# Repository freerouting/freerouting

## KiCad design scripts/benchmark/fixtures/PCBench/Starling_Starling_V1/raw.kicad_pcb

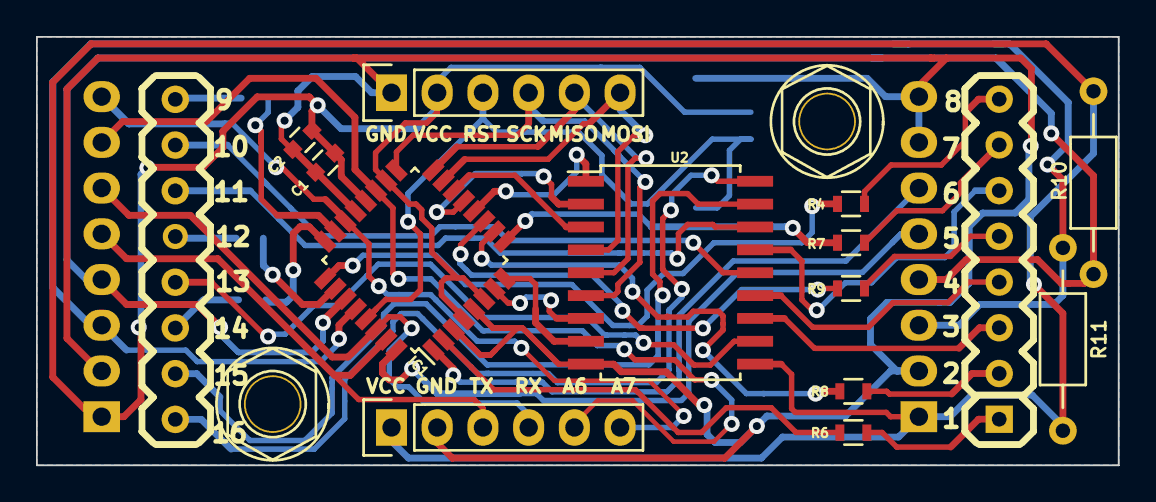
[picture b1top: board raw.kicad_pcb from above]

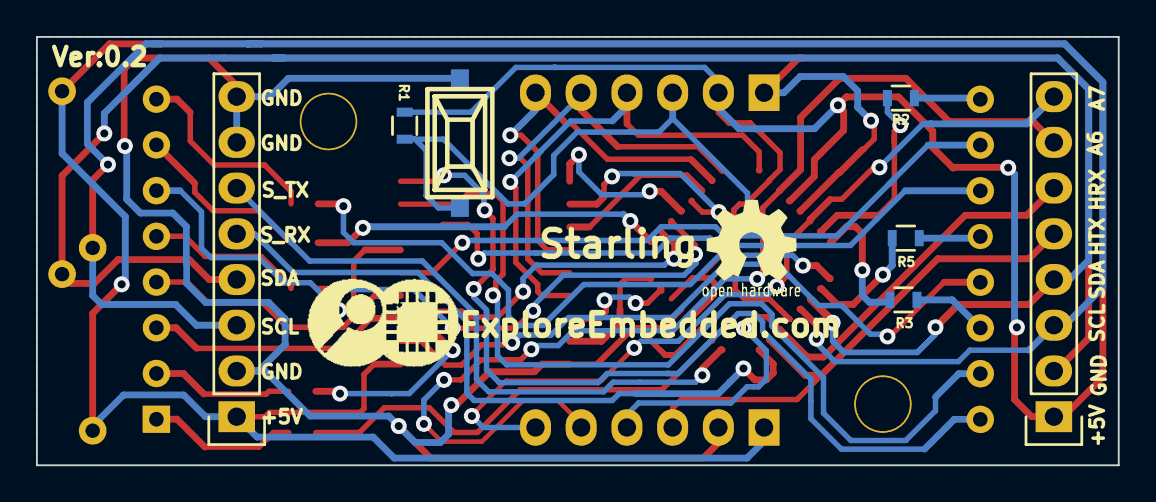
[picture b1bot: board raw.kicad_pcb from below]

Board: 2 copper layers, 60.1 x 23.8 mm, 24 parts (8 on the bottom side), 43 nets.

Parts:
C1, C2: 0.1uF; C_0603
IC1: ATMEGA8-AI; LQFP-32_7x7mm_Pitch0.8mm
LOGO: LOGO (2)
P1, P2: CONN_01X01; M3_mounting
P3, P6: CONN_01X06; Pin_Header_Straight_1x06
P4, P5: CONN_01X08; Pin_Header_Straight_1x08
R1: 10K; R_0603
R2, R3, R4, R5, R6, R7, R8, R9: 22r; R_0603
R10, R11: 10K; Resistor_Horizontal_RM10mm
SW1: SPST; smd_push
U1: 8x8_Row_anode; 8X8_matrix_2.3inch
U2: ULN2803; SOIC-18_7.5x11.6mm_Pitch1.27mm

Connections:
+5C: C1.1, C2.1, IC1.4, IC1.6, IC1.18, IC1.20, P3.2, P4.1, P5.1, P6.1, R1.1, R10.1, R11.1, U2.10
/ADC6: IC1.19, P4.7, P6.5
/ADC7: IC1.22, P4.8, P6.6
/H_RX: IC1.30, P4.6, P6.4
/H_TX: IC1.31, P4.5, P6.3
/MISO: IC1.16, P3.5, U2.5
/MOSI: IC1.15, P3.6, U2.4
/PB6: IC1.7, U2.7
/PB7: IC1.8, U2.8
/RST: IC1.29, P3.3, R1.2, SW1.2
/SCK: IC1.17, P3.4, U2.6
/SCL: IC1.28, P4.3, P5.3, R11.2
/SDA: IC1.27, P4.4, P5.4, R10.2
/S_RX: IC1.32, P5.5
/S_TX: IC1.1, P5.6
GND: C1.2, C2.2, IC1.3, IC1.5, IC1.21, P3.1, P4.2, P5.2, P5.7, P5.8, P6.2, SW1.1, U2.9
unnamed: IC1.2, R6.2
unnamed: IC1.9, R7.2
unnamed: IC1.10, R8.2
unnamed: IC1.11, R9.2
unnamed: IC1.12, U2.1
unnamed: IC1.13, U2.2
unnamed: IC1.14, U2.3
unnamed: IC1.23, R2.2
unnamed: IC1.24, R3.2
unnamed: IC1.25, R4.2
unnamed: IC1.26, R5.2
unnamed: R2.1, U1.9
unnamed: R3.1, U1.14
unnamed: R4.1, U1.8
unnamed: R5.1, U1.12
unnamed: R6.1, U1.1
unnamed: R7.1, U1.7
unnamed: R8.1, U1.2
unnamed: R9.1, U1.5
unnamed: U1.3, U2.12
unnamed: U1.4, U2.13
unnamed: U1.6, U2.15
unnamed: U1.10, U2.14
unnamed: U1.11, U2.16
unnamed: U1.13, U2.11
unnamed: U1.15, U2.17
unnamed: U1.16, U2.18

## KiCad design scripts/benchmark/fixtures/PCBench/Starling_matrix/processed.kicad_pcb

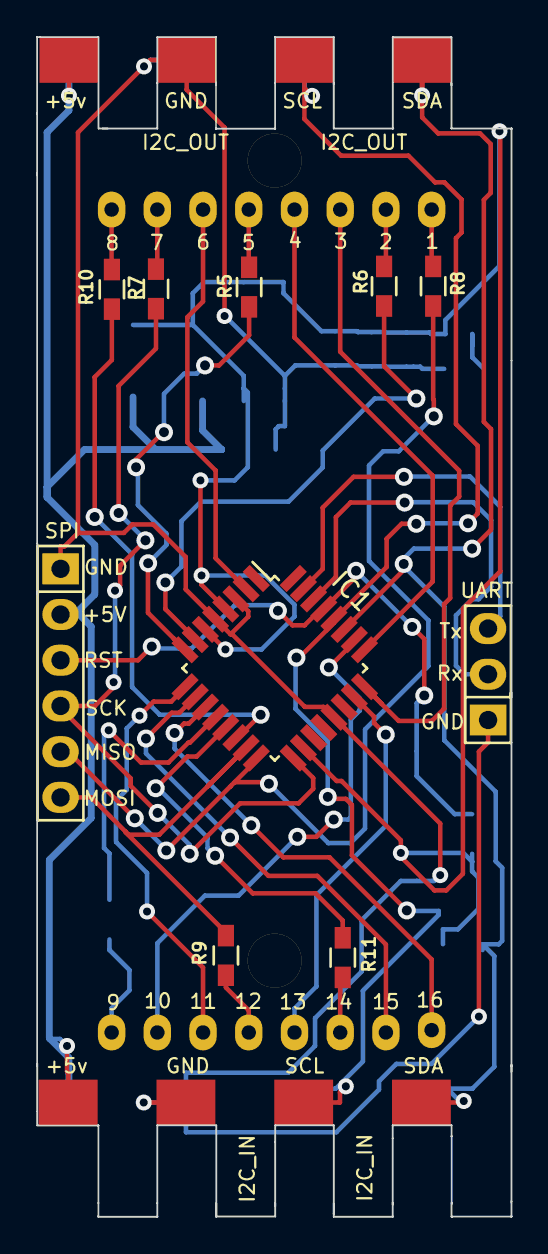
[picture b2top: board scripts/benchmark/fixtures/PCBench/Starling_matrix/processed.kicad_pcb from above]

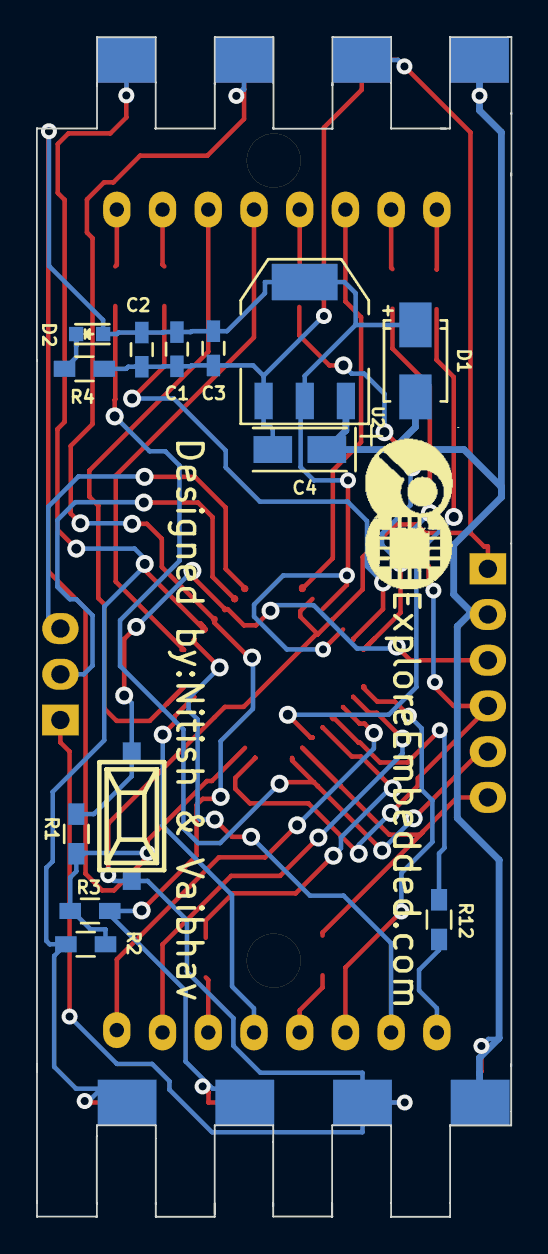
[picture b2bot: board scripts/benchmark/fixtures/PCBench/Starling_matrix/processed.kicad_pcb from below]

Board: 2 copper layers, 26.4 x 65.6 mm, 29 parts (14 on the bottom side), 33 nets.

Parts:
C1, C2, C3: 0.1uf; C_0603_HandSoldering
C4: 10uF; TantalC_SizeA_EIA-3216_Wave
D1: DIODE; SMA_Standard
D2: LED; LED-0603
IC1: ATMEGA8-AI; TQFP-32_7x7mm_Pitch0.8mm
LOGO: LOGO (2)
P1: CONN_01X06; Pin_Header_Straight_1x06
P2, P3: CONN_01X04; matrix_connector
P4: CONN_01X03; Pin_Header_Straight_1x03
P5, P6: CONN_01X01; 1pin
R1, R2, R3: 10K; R_0603_HandSoldering
R4: 470E; R_0603_HandSoldering
R5, R6, R7, R8, R9, R10, R11, R12: 22E; R_0603_HandSoldering
SW1: SPST; smd_push
U1: DispHB2388; 8x8dot matrix
U2: lm1117/3.3; lm117_SOT-223

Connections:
+3V3: C1.1, C2.1, C3.1, D1.1, D2.1, IC1.4, IC1.6, IC1.18, R1.1, R2.1, R3.1, U2.2, U2.4
+5V: C4.1, D1.2, P1.2, P2.1, P3.1, U2.3
/MISO: IC1.16, P1.5, R8.1
/MOSI: IC1.15, P1.6, R9.1
/PB6: IC1.7, R6.1
/PB7: IC1.8, R5.1
/RST: IC1.29, P1.3, R1.2, SW1.2
/Rx: IC1.30, P4.2
/SCK: IC1.17, P1.4, R7.1
/SCL: IC1.28, P2.3, P3.3, R3.2
/SDA: IC1.27, P2.4, P3.4, R2.2
/Tx: IC1.31, P4.3
GND: C1.2, C2.2, C3.2, C4.2, IC1.3, IC1.5, IC1.21, P1.1, P2.2, P3.2, P4.1, R4.2, SW1.1, U2.1
unnamed: D2.2, R4.1
unnamed: IC1.2, U1.6
unnamed: IC1.9, U1.11
unnamed: IC1.10, U1.15
unnamed: IC1.11, U1.16
unnamed: IC1.12, R12.1
unnamed: IC1.13, R11.1
unnamed: IC1.14, R10.1
unnamed: IC1.23, U1.13
unnamed: IC1.24, U1.3
unnamed: IC1.25, U1.4
unnamed: IC1.26, U1.10
unnamed: R5.2, U1.5
unnamed: R6.2, U1.2
unnamed: R7.2, U1.7
unnamed: R8.2, U1.1
unnamed: R9.2, U1.12
unnamed: R10.2, U1.8
unnamed: R11.2, U1.14
unnamed: R12.2, U1.9

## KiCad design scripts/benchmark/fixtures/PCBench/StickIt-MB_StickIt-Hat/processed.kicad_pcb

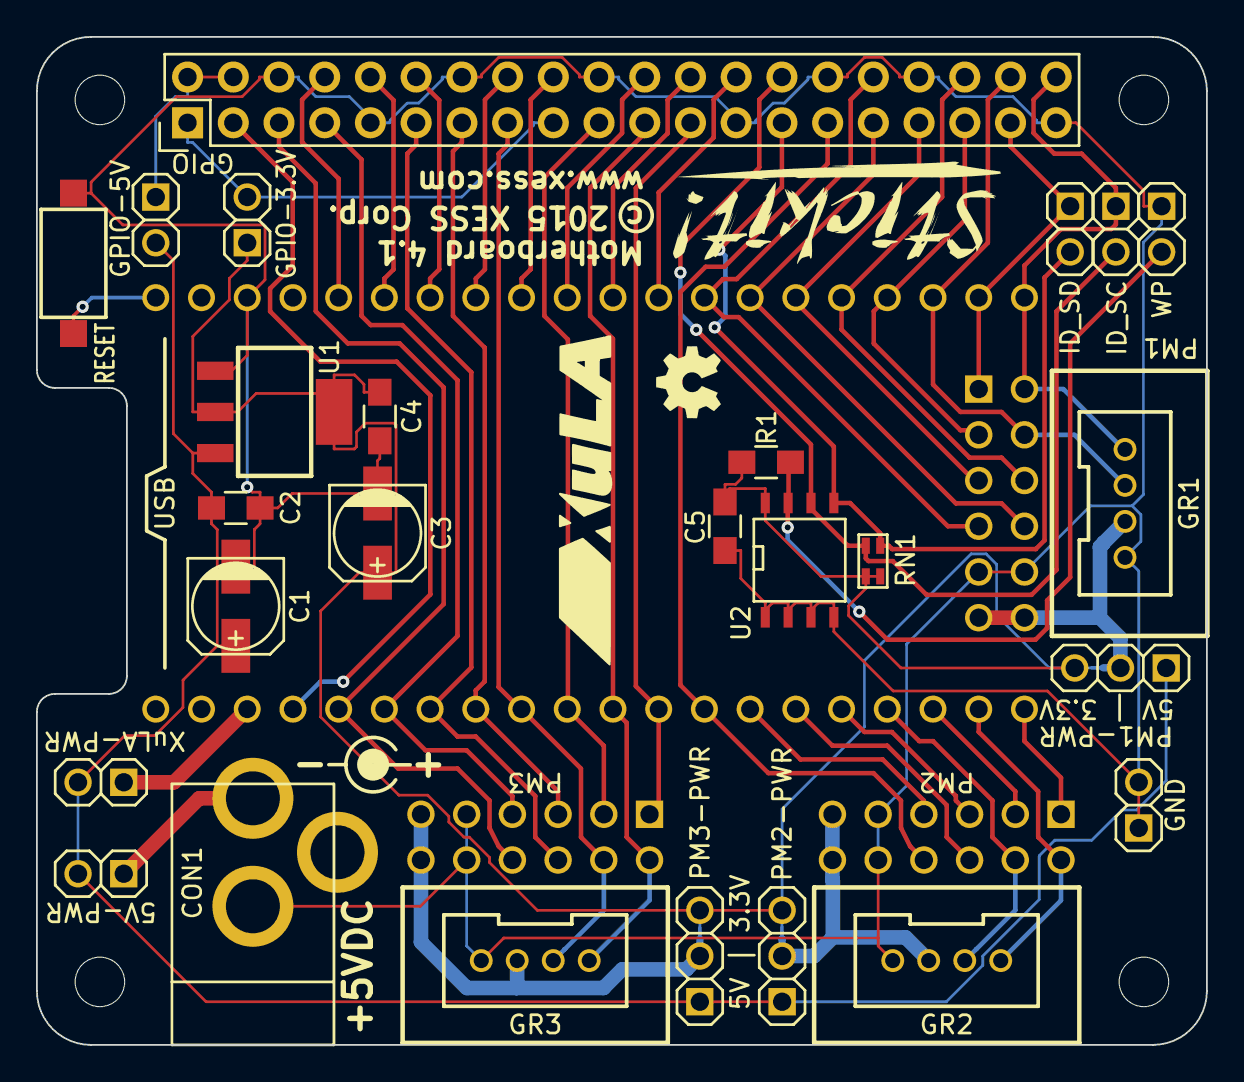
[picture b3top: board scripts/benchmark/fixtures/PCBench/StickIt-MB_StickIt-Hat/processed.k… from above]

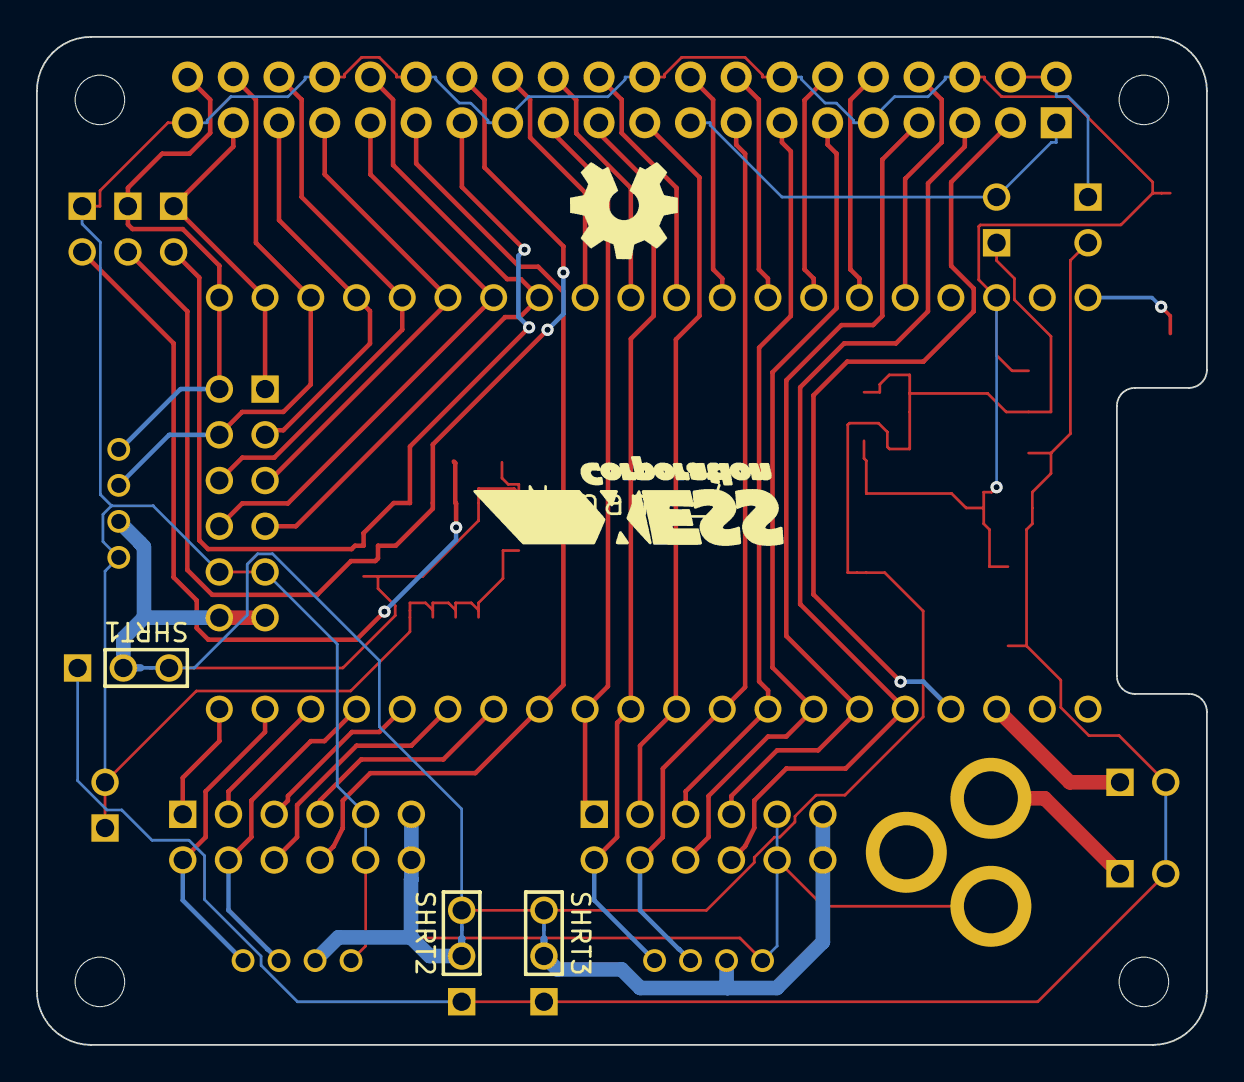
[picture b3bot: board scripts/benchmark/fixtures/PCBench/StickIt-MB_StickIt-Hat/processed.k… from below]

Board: 2 copper layers, 65.0 x 56.0 mm, 41 parts (5 on the bottom side), 47 nets.

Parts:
C1, C3: 22uF; c_elec_5x5.3
C2, C4: 4.7uF; R_0805_HandSoldering
C5: 0.1uF; R_0805_HandSoldering
CON1: BARREL_JACK
GPIO1: RPi_GPIO; Pin_Header_Straight_2x20
GR1, GR2, GR3: Grove; GROVE_MALE
J1: XuLA_IO_HDR; XuLA_IO_Hdr
J3, J4, J5: JSHORTNORMAL; xess-JSHORT
JP1, JP2, JP3: JUMPER3; HDR_1x3
JP4, JP5, JP6, JP7, JP8, JP9, JP10: JUMPER; HDR_1x2
Noname_1: oshw_logo_4mm
Noname_2: stickit_logo_18mm
Noname_3: oshw_logo_6mm
Noname_4: xesscorp2
Noname_5, Noname_6, Noname_7, Noname_8: RPi_Hat_Mounting_Hole
PM1, PM2, PM3: PMOD_SCKT-12
R1: 1K; R_0805_HandSoldering
RN1: 3.9K; CTS_742C043
SW1: SW_PUSH; RS-282G05A3-SM_RT
TP1: JUMPER; HDR_1x2
U1: NCV1117; SOT-223
U2: CAT24C32; SOIC-8-N

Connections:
+3.3V: C3.1, C4.1, C5.1, J3.2, J4.2, J5.2, JP1.3, JP2.3, JP3.3, JP7.1, R1.1, RN1.1, RN1.2, U1.2, U1.4, U2.8
+3.3V-RPi: GPIO1.1, GPIO1.17, JP7.2
+5V: C1.1, C2.1, JP1.1, JP2.1, JP3.1, JP4.2, JP5.2, JP6.2, U1.3
+5V-RPi: GPIO1.2, GPIO1.4, JP4.1
+5V-XuLA: J1.3, JP5.1
CHAN0: GPIO1.37, J1.22, JP10.1, PM1.1
CHAN1: GPIO1.38, GR1.2, J1.23, PM1.8
CHAN2: GPIO1.35, J1.24, PM1.2
CHAN3: GPIO1.36, J1.25, PM1.9
CHAN4: GPIO1.33, J1.26, PM1.3
CHAN5: GPIO1.31, J1.27, PM1.10
CHAN6: GPIO1.32, J1.28, PM1.4
CHAN7: GPIO1.26, J1.29
CHAN8: GPIO1.24, J1.30
CHAN9: GPIO1.22, J1.31
CHAN10: GPIO1.18, J1.32
CHAN11: GPIO1.16, J1.33
CHAN12: GPIO1.12, J1.34
CHAN13: GPIO1.10, J1.35
CHAN14: GPIO1.8, J1.36
CHAN15: J1.20, PM2.1
CHAN16: GR2.1, J1.19, PM2.7
CHAN17: J1.18, PM2.2
CHAN18: GR2.2, J1.17, PM2.8
CHAN19: J1.16, PM2.3
CHAN20: J1.15, PM2.9
CHAN21: J1.14, PM2.4
CHAN22: GPIO1.29, J1.13, PM2.10
CHAN23: GPIO1.23, J1.12, PM3.1
CHAN24: GPIO1.21, GR3.1, J1.11, PM3.7
CHAN25: GPIO1.19, J1.10, PM3.2
CHAN26: GPIO1.15, GR3.2, J1.9, PM3.8
CHAN27: GPIO1.13, J1.8, PM3.3
CHAN28: GPIO1.11, J1.7, PM3.9
CHAN29: GPIO1.7, J1.6, PM3.4
CHAN30: GPIO1.5, J1.5, PM3.10
CHAN31: GPIO1.3, J1.4
CHANCLK: GPIO1.40, GR1.1, J1.21, JP9.1, PM1.7
GND: C1.2, C2.2, C3.2, C4.2, C5.2, CON1.2, GPIO1.6, GPIO1.9, GPIO1.14, GPIO1.20, GPIO1.25, GPIO1.30, GPIO1.34, GPIO1.39, GR1.4, GR2.4, GR3.4, J1.38, JP8.1, PM1.5, PM1.11, PM2.5, PM2.11, PM3.5, PM3.11, SW1.2, TP1.1, TP1.2, U1.1, U2.1, U2.2, U2.3, U2.4
ID_SC: GPIO1.28, JP9.2, RN1.4, U2.6
ID_SD: GPIO1.27, JP10.2, RN1.3, U2.5
unnamed: CON1.1, JP6.1
unnamed: GR1.3, J3.1, JP1.2, PM1.6, PM1.12
unnamed: GR2.3, J4.1, JP2.2, PM2.6, PM2.12
unnamed: GR3.3, J5.1, JP3.2, PM3.6, PM3.12
unnamed: J1.40, SW1.1
unnamed: JP8.2, R1.2, U2.7

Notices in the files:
scripts/benchmark/fixtures/PCBench/StickIt-MB_StickIt-Hat/processed.kicad_pcb:
(c) 2015
